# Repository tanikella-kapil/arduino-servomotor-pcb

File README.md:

# arduino-servomotor-pcb
# arduino-servomotor-pcb

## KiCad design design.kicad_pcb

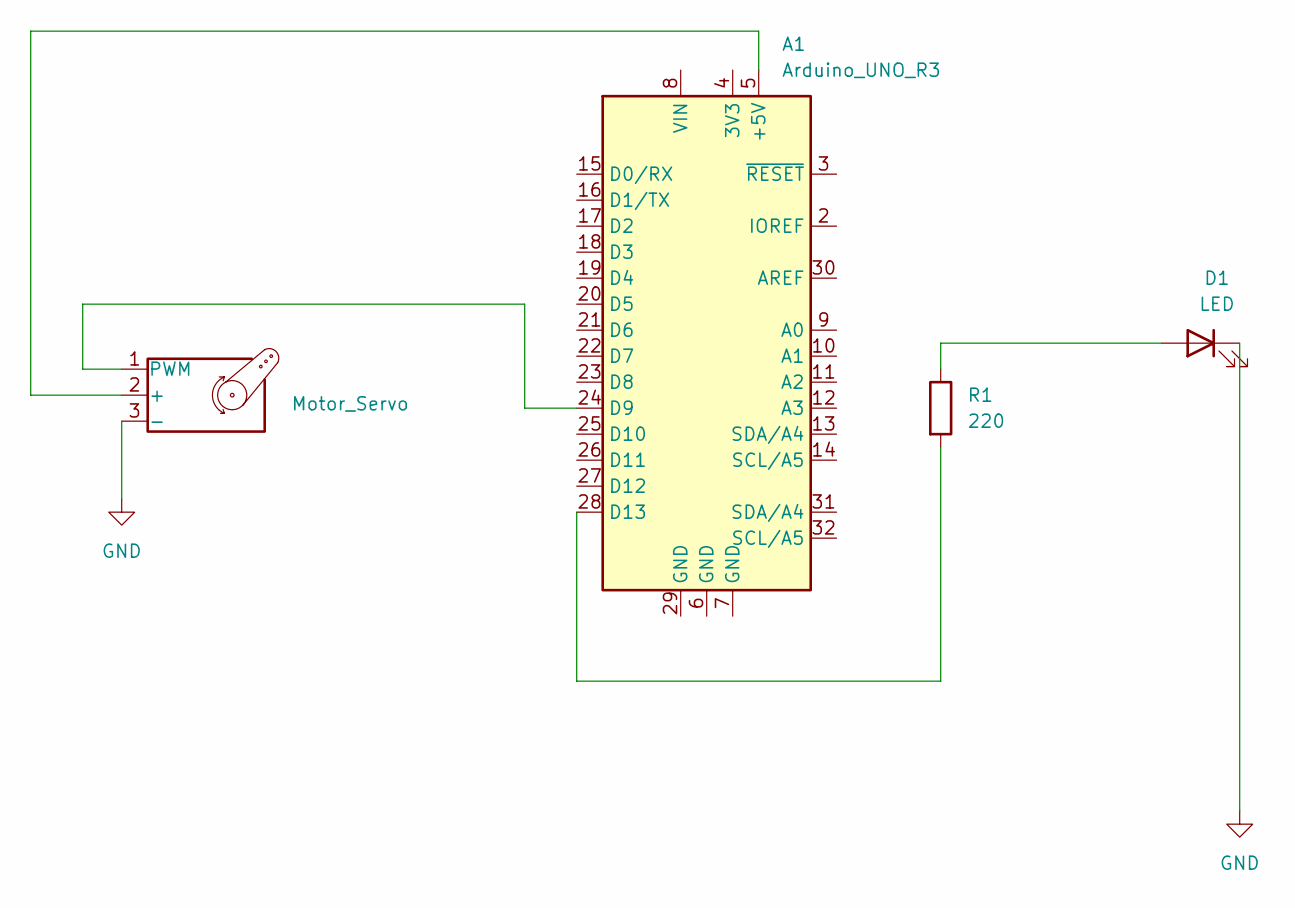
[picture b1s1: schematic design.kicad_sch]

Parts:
A1: Arduino_UNO_R3
D1: LED; LED_D5.0mm_FlatTop
M1: Motor_Servo; PinHeader_1x03_P2.54mm_Vertical
R1: 220; R_Axial_DIN0207_L6.3mm_D2.5mm_P7.62mm_Horizontal

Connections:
GND: D1.1 (K), M1.3 (-)
unnamed: A1.5 (+5V), M1.2 (+)
unnamed: A1.24 (D9), M1.1 (PWM)
unnamed: A1.28 (D13), R1.2
unnamed: D1.2 (A), R1.1

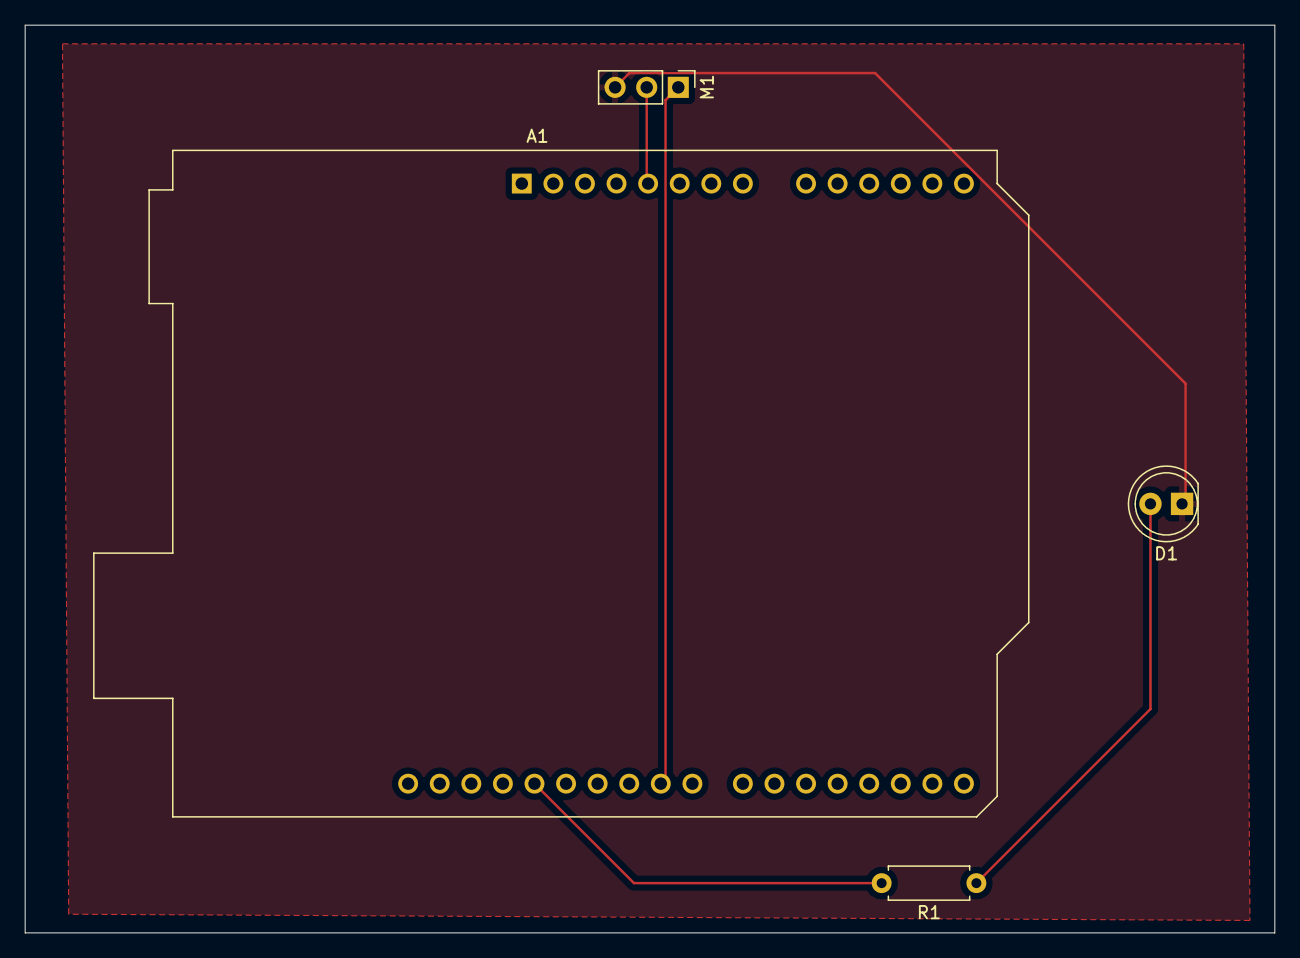
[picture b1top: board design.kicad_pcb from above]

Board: 2 copper layers, 100.5 x 73.0 mm, 4 parts (0 on the bottom side), 5 nets.
